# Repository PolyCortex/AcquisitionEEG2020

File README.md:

<h1 align="center">
  <br>
  
  <br>
  Acquisition board 2020
  <br>
</h1>

<h4 align="center">A 4-channels biosignal acquisition pipeline.</h4>
<p align="center">
  
 </p>

<p align="center">
  <a href="#key-features">Key Features</a> •
  <a href="#how-it-works">How It Works</a> •
  <a href="#project-structure">Project Structure</a> •
  <a href="#learn-more">Learn more</a> •
  <a href="#learn-more">About us</a>
</p>

---

The project contained in this repository is a 4-channel prototype board produced in the development of a PCB to acquire EEG signals. It contains an instrumentation amplifier, a notch filter and an anti aliasing filter. It is designed to be sampled either in a lab with the help of an oscilloscope or with a computer through a Teensy 3.2 microcontroller development board. As well, a signal visualization software can analyze the signal coming from this board.

**Disclaimer:** This prototype board does not work to sample EEG signals and was never intended as such. It was meant to be a platform used to test designs of filtering and amplification circuits, which we would have integrated into a true production PCB. However, our development cycle was slowed down due to the pandemic and we had to plan the release of the production version of the board for April 2021 instead. Even though we did not finish the project, we still wanted to show our progress and so we submit this prototype for the NeuroTechX 2020 Fixed Challenge.

## Key features

- A PCB which amplifies the signals and filters them through an analog acquisition pipeline.
- A realtime data acquisition software that can records, save, perform machine learning and neuroscience experiments.

## How it works

### Acquisition

The board includes four channels and so five electrodes should be placed on the patient's head: one per channel and a fifth reference electrode. The reference electrode is clipped at the patient's ear and voltages from the channel electrodes are measured against it.

### Signal processing

The full processing pipeline for EEG includes and instrumentation amplifier, which the measurement of extremely small EEG voltages. The pipeline also includes a high pass filter, a notch filter and a low pass filter which each eliminate different types of noise from the signal. 

### Data Transmission

After having been processed, the data is digitized by a microcontroller's Analog to Digital Converter (ADC) and sent to a computer.
Data from the board is received on the computer via one of its USB serial port. 

### Real-time visualization

The realtime visualization software can read the flow of data coming from the serial port and plot the signal on every channel in realtime. It can also show the data in the frequency domain using spectral, spectrogram and power band reprensentations.

### Data recording

All the raw data coming from the board can then be saved in a csv file for subsequent use.

## Project Structure

- The `cad/` folder contains files used to make the PCBs. The prototype board is under `cad/prototype-board/`. Two supply prototypes are included under `cad/supply-analog/` and `cad/supply-digital/`.
- The `components/` folder contains the datasheets for important components.
- The `simulations/` folder contains ltspice simulations for the elements of the analog processing pipeline.
- The `software/` folder contains everything that is linked to software. The computer software for digital signal processing and realtime visualization is under `software/gui/`. Check it out for more information about it. The microcontroller software for sampling the analog signals and to stream them to the computer is under  `software/teensy-code/`.

## Learn more

You can read more about the technical aspect of the prototype board, and of the planned production board in this
[wiki](https://github.com/PolyCortex/AcquisitionEEG2020/wiki).

## About us

[PolyCortex](http://polycortex.polymtl.ca/) is a student club based at [Polytechnique Montreal](https://www.polymtl.ca/).

The goal of PolyCortex is to develop expertise in neuroscience and engineering to solve neuroengineering problems. This field aims to create technological solutions dedicated to the search for innovative solutions to neuroscience problems.

To do this, we recommend the use of solutions revolving around the design of brain-machine interface devices, the implementation of embedded systems, the use of machine learning and signal processing techniques.

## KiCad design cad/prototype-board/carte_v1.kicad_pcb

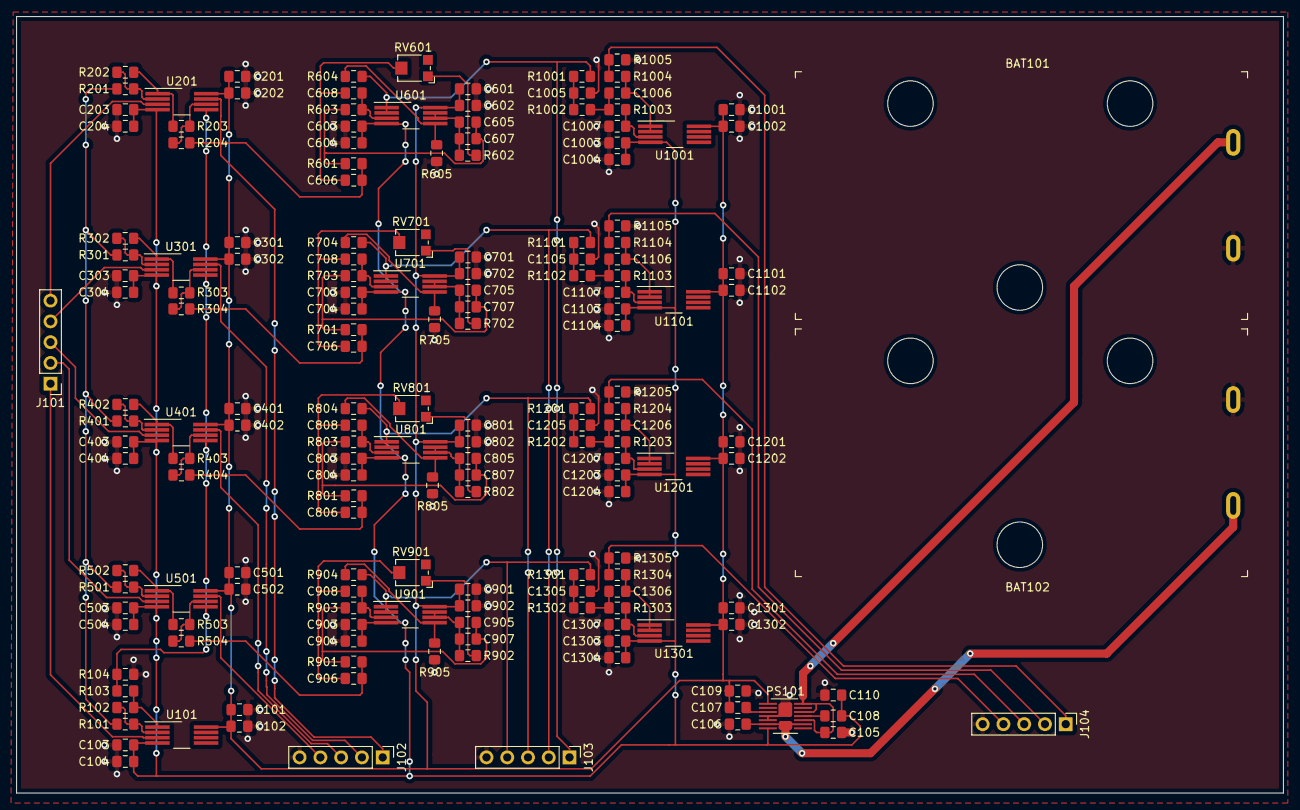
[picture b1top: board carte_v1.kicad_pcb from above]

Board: 2 copper layers, 155.0 x 95.0 mm, 170 parts (0 on the bottom side), 80 nets.

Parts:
BAT101, BAT102: BC9VPC; Battery_Holder_9V_BC9VPC-ND
C101, C102, C103, C104, C201, C202, C203, C204, C301, C302, C303, C304, C401, C402, C403, C404, C501, C502, C503, C504, C601, C602, C603, C604, C605, C606, C607, C608, C701, C702, C703, C704, C705, C706, C707, C708, C801, C802, C803, C804, C805, C806, C807, C808, C901, C902, C903, C904, C905, C906, C907, C908, C1001, C1002, C1003, C1004, C1005, C1006, C1101, C1102, C1103, C1104, C1105, C1106, C1201, C1202, C1203, C1204, C1205, C1206, C1301, C1302, C1303, C1304, C1305, C1306: 0.1uF; C_0805_2012Metric_Pad1.15x1.40mm_HandSolder
C105, C106, C109, C110: 10uF; C_0805_2012Metric_Pad1.15x1.40mm_HandSolder
C107, C108: 0.01uF; C_0805_2012Metric_Pad1.15x1.40mm_HandSolder
C1007, C1107, C1207, C1307: 0.015uF; C_0805_2012Metric_Pad1.15x1.40mm_HandSolder
J101: INPUTS; PinHeader_1x05_P2.54mm_Vertical
J102: POST_INSTR; PinHeader_1x05_P2.54mm_Vertical
J103: POST_NOTCH; PinHeader_1x05_P2.54mm_Vertical
J104: OUTPUTS; PinHeader_1x05_P2.54mm_Vertical
PS101: LT3032-5; Linear_DE14MA_manual_soldering
R101, R201, R301, R401, R501: 1k; R_0805_2012Metric_Pad1.15x1.40mm_HandSolder
R102, R103, R104, R202, R203, R204, R302, R303, R304, R402, R403, R404, R502, R503, R504: 1M; R_0805_2012Metric_Pad1.15x1.40mm_HandSolder
R601, R603, R701, R703, R801, R803, R901, R903: 26.1k; R_0805_2012Metric_Pad1.15x1.40mm_HandSolder
R602, R605, R702, R705, R802, R805, R902, R905, R1005, R1105, R1205, R1305: 10k; R_0805_2012Metric_Pad1.15x1.40mm_HandSolder
R604, R704, R804, R904: 422; R_0805_2012Metric_Pad1.15x1.40mm_HandSolder
R1001, R1101, R1201, R1301: 1.8k; R_0805_2012Metric_Pad1.15x1.40mm_HandSolder
R1002, R1102, R1202, R1302: 5.1k; R_0805_2012Metric_Pad1.15x1.40mm_HandSolder
R1003, R1103, R1203, R1303: 3k; R_0805_2012Metric_Pad1.15x1.40mm_HandSolder
R1004, R1104, R1204, R1304: 249; R_0805_2012Metric_Pad1.15x1.40mm_HandSolder
RV601, RV701, RV801, RV901: R_POT_TRIM_US; Potentiometer_Bourns_TC33X_Vertical
U101, U201, U301, U401, U501, U601, U701, U801, U901, U1001, U1101, U1201, U1301: OPA2202; VSSOP-8_3.0x3.0mm_P0.65mm_manual_soldering

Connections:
+5V: C101.2, C102.2, C107.1, C109.1, C201.2, C202.2, C301.2, C302.2, C401.2, C402.2, C501.2, C502.2, C601.2, C602.2, C701.2, C702.2, C801.2, C802.2, C901.2, C902.2, C1001.2, C1002.2, C1101.2, C1102.2, C1201.2, C1202.2, C1301.2, C1302.2, PS101.1, U101.8, U201.8, U301.8, U401.8, U501.8, U601.8, U701.8, U801.8, U901.8, U1001.8, U1101.8, U1201.8, U1301.8
+9V: BAT101.POS, C105.1, PS101.10, PS101.12, PS101.14
-5V: C103.2, C104.2, C108.2, C110.2, C203.2, C204.2, C303.2, C304.2, C403.2, C404.2, C503.2, C504.2, C603.2, C604.2, C703.2, C704.2, C803.2, C804.2, C903.2, C904.2, C1003.2, C1004.2, C1103.2, C1104.2, C1203.2, C1204.2, C1303.2, C1304.2, PS101.7, U101.4, U201.4, U301.4, U401.4, U501.4, U601.4, U701.4, U801.4, U901.4, U1001.4, U1101.4, U1201.4, U1301.4
-9V: BAT102.NEG, C106.2, PS101.6, PS101.9
/InstrAmpChannel1/IN: J101.5, U201.3
/InstrAmpChannel1/STG1COMMON: R101.2, R201.2, R301.2, R401.2, R501.2
/InstrAmpChannel1/STG2COMMON: R103.1, R104.2, U201.5, U301.5, U401.5, U501.5
/InstrAmpChannel2/IN: J101.4, U301.3
/InstrAmpChannel3/IN: J101.3, U401.3
/InstrAmpChannel4/IN: J101.2, U501.3
/LPFilter1/IN: J103.1, R604.2, R1001.2, U601.1, U601.2
/LPFilter1/OUT: J104.1, R1004.1, R1005.2
/LPFilter2/IN: J103.2, R704.2, R1101.2, U701.1, U701.2
/LPFilter2/OUT: J104.2, R1104.1, R1105.2
/LPFilter3/IN: J103.3, R804.2, R1201.2, U801.1, U801.2
/LPFilter3/OUT: J104.3, R1204.1, R1205.2
/LPFilter4/IN: J103.4, R904.2, R1301.2, U901.1, U901.2
/LPFilter4/OUT: J104.4, R1304.1, R1305.2
/NotchFilter1/IN: C606.2, J102.1, R204.1, R601.2, U201.7
/NotchFilter2/IN: C706.2, J102.2, R304.1, R701.2, U301.7
/NotchFilter3/IN: C806.2, J102.3, R404.1, R801.2, U401.7
/NotchFilter4/IN: C906.2, J102.4, R504.1, R901.2, U501.7
GND: BAT101.NEG, BAT102.POS, C101.1, C102.1, C103.1, C104.1, C105.2, C106.1, C109.2, C110.1, C201.1, C202.1, C203.1, C204.1, C301.1, C302.1, C303.1, C304.1, C401.1, C402.1, C403.1, C404.1, C501.1, C502.1, C503.1, C504.1, C601.1, C602.1, C603.1, C604.1, C701.1, C702.1, C703.1, C704.1, C801.1, C802.1, C803.1, C804.1, C901.1, C902.1, C903.1, C904.1, C1001.1, C1002.1, C1003.1, C1004.1, C1005.2, C1007.2, C1101.1, C1102.1, C1103.1, C1104.1, C1105.2, C1107.2, C1201.1, C1202.1, C1203.1, C1204.1, C1205.2, C1207.2, C1301.1, C1302.1, C1303.1, C1304.1, C1305.2, C1307.2, J102.5, J103.5, J104.5, PS101.4, PS101.5, R104.1, R605.1, R705.1, R805.1, R905.1, R1005.1, R1105.1, R1205.1, R1305.1
unnamed: C107.2, PS101.3
unnamed: C108.1, PS101.11
unnamed: C605.1, C607.1, R601.1, R603.2
unnamed: C605.2, C607.2, R602.1, U601.6, U601.7
unnamed: C606.1, C608.2, RV601.2
unnamed: C608.1, R603.1, U601.3
unnamed: C705.1, C707.1, R701.1, R703.2
unnamed: C705.2, C707.2, R702.1, U701.6, U701.7
unnamed: C706.1, C708.2, RV701.2
unnamed: C708.1, R703.1, U701.3
unnamed: C805.1, C807.1, R801.1, R803.2
unnamed: C805.2, C807.2, R802.1, U801.6, U801.7
unnamed: C806.1, C808.2, RV801.2
unnamed: C808.1, R803.1, U801.3
unnamed: C905.1, C907.1, R901.1, R903.2
unnamed: C905.2, C907.2, R902.1, U901.6, U901.7
unnamed: C906.1, C908.2, RV901.2
unnamed: C908.1, R903.1, U901.3
unnamed: C1005.1, R1001.1, R1002.2
unnamed: C1006.1, R1002.1, R1003.2
unnamed: C1006.2, R1004.2, U1001.1, U1001.2
unnamed: C1007.1, R1003.1, U1001.3
unnamed: C1105.1, R1101.1, R1102.2
unnamed: C1106.1, R1102.1, R1103.2
unnamed: C1106.2, R1104.2, U1101.1, U1101.2
unnamed: C1107.1, R1103.1, U1101.3
unnamed: C1205.1, R1201.1, R1202.2
unnamed: C1206.1, R1202.1, R1203.2
unnamed: C1206.2, R1204.2, U1201.1, U1201.2
unnamed: C1207.1, R1203.1, U1201.3
unnamed: C1305.1, R1301.1, R1302.2
unnamed: C1306.1, R1302.1, R1303.2
unnamed: C1306.2, R1304.2, U1301.1, U1301.2
unnamed: C1307.1, R1303.1, U1301.3
unnamed: J101.1, U101.3
unnamed: R101.1, R102.2, U101.2
unnamed: R102.1, R103.2, U101.1
unnamed: R201.1, R202.2, U201.2
unnamed: R202.1, R203.2, U201.1
unnamed: R203.1, R204.2, U201.6
unnamed: R301.1, R302.2, U301.2
unnamed: R302.1, R303.2, U301.1
unnamed: R303.1, R304.2, U301.6
unnamed: R401.1, R402.2, U401.2
unnamed: R402.1, R403.2, U401.1
unnamed: R403.1, R404.2, U401.6
unnamed: R501.1, R502.2, U501.2
unnamed: R502.1, R503.2, U501.1
unnamed: R503.1, R504.2, U501.6
unnamed: R602.2, RV601.1
unnamed: R604.1, R605.2, U601.5
unnamed: R702.2, RV701.1
unnamed: R704.1, R705.2, U701.5
unnamed: R802.2, RV801.1
unnamed: R804.1, R805.2, U801.5
unnamed: R902.2, RV901.1
unnamed: R904.1, R905.2, U901.5

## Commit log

2020-11-22 Release 2020 Acquisition GUI
2020-11-22 Fixed submodule gui/
2020-11-23 project commit
2020-11-23 add lm321
2020-11-23 remove virtualenv
2020-11-23 update gui readme
2020-11-23 Add template for readme
2020-11-23 add about us badge
2021-03-26 Bump pyyaml from 5.1 to 5.4 in /software/gui
    Bumps [pyyaml](https://github.com/yaml/pyyaml) from 5.1 to 5.4.
    - [Release notes](https://github.com/yaml/pyyaml/releases)
    - [Changelog](https://github.com/yaml/pyyaml/blob/master/CHANGES)
    - [Commits](https://github.com/yaml/pyyaml/compare/5.1...5.4)
2022-09-23 Bump protobuf from 3.7.0 to 3.18.3 in /software/gui
    Bumps [protobuf](https://github.com/protocolbuffers/protobuf) from 3.7.0 to 3.18.3.
    - [Release notes](https://github.com/protocolbuffers/protobuf/releases)
    - [Changelog](https://github.com/protocolbuffers/protobuf/blob/main/generate_changelog.py)
    - [Commits](https://github.com/protocolbuffers/protobuf/compare/v3.7.0...v3.18.3)
    ---
    updated-dependencies:
